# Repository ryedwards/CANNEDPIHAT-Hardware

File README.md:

# CANNEDPIHAT-Hardware

## The CannedPi Hardware
Meet the CannedPi hardware!  This simple (and not prefectly designed) Raspberry PI Hat contains an STM32G4 microcontroller which can interface with the USB port of your Pi.

Why would I create such a Rube Goldberg design??
- I wanted a HAT that would provide provide solid 5V power from a ~12V power input.  This board has a 4A SMPS that provides more than enough juice for even a power hungry Pi4.
- I wanted the option of running both scripts on the Pi (Python-CAN, C applications, etc) while also having the ability to run real-time CAN on the embedded chip as needed.
- Wanted an "all-in-one" form factor for mounting on LCD displays and other small cases
- For LIN you really need the real time microcontroller
- I wanted to prove I could do it.  Now that I feel I've achived my goal I decided to share it wth everyone

## Features
- The 26-pin header provides access to all 3 CAN channels, the LIN channel, 12V, 5V, 3.3V and a few GPIO from both the PI and the SMT32G4.  Why a 26-pin?  Other CAN tools I'm using also utilize this header and I didn't feel like making new harnesses.  Besides, it's a nice form factor for getting a lot of I/O and there are cables available on Amazon.

## Notes
This design is provided in KiCad 6.0

## Disclaimers
It has not been EMI or EMC tested.  I am not a hardware engineer so I can't ensure that there aren't some design flaws.  I've sanity tested the prototypes and they seem to be stable and perform as expected.

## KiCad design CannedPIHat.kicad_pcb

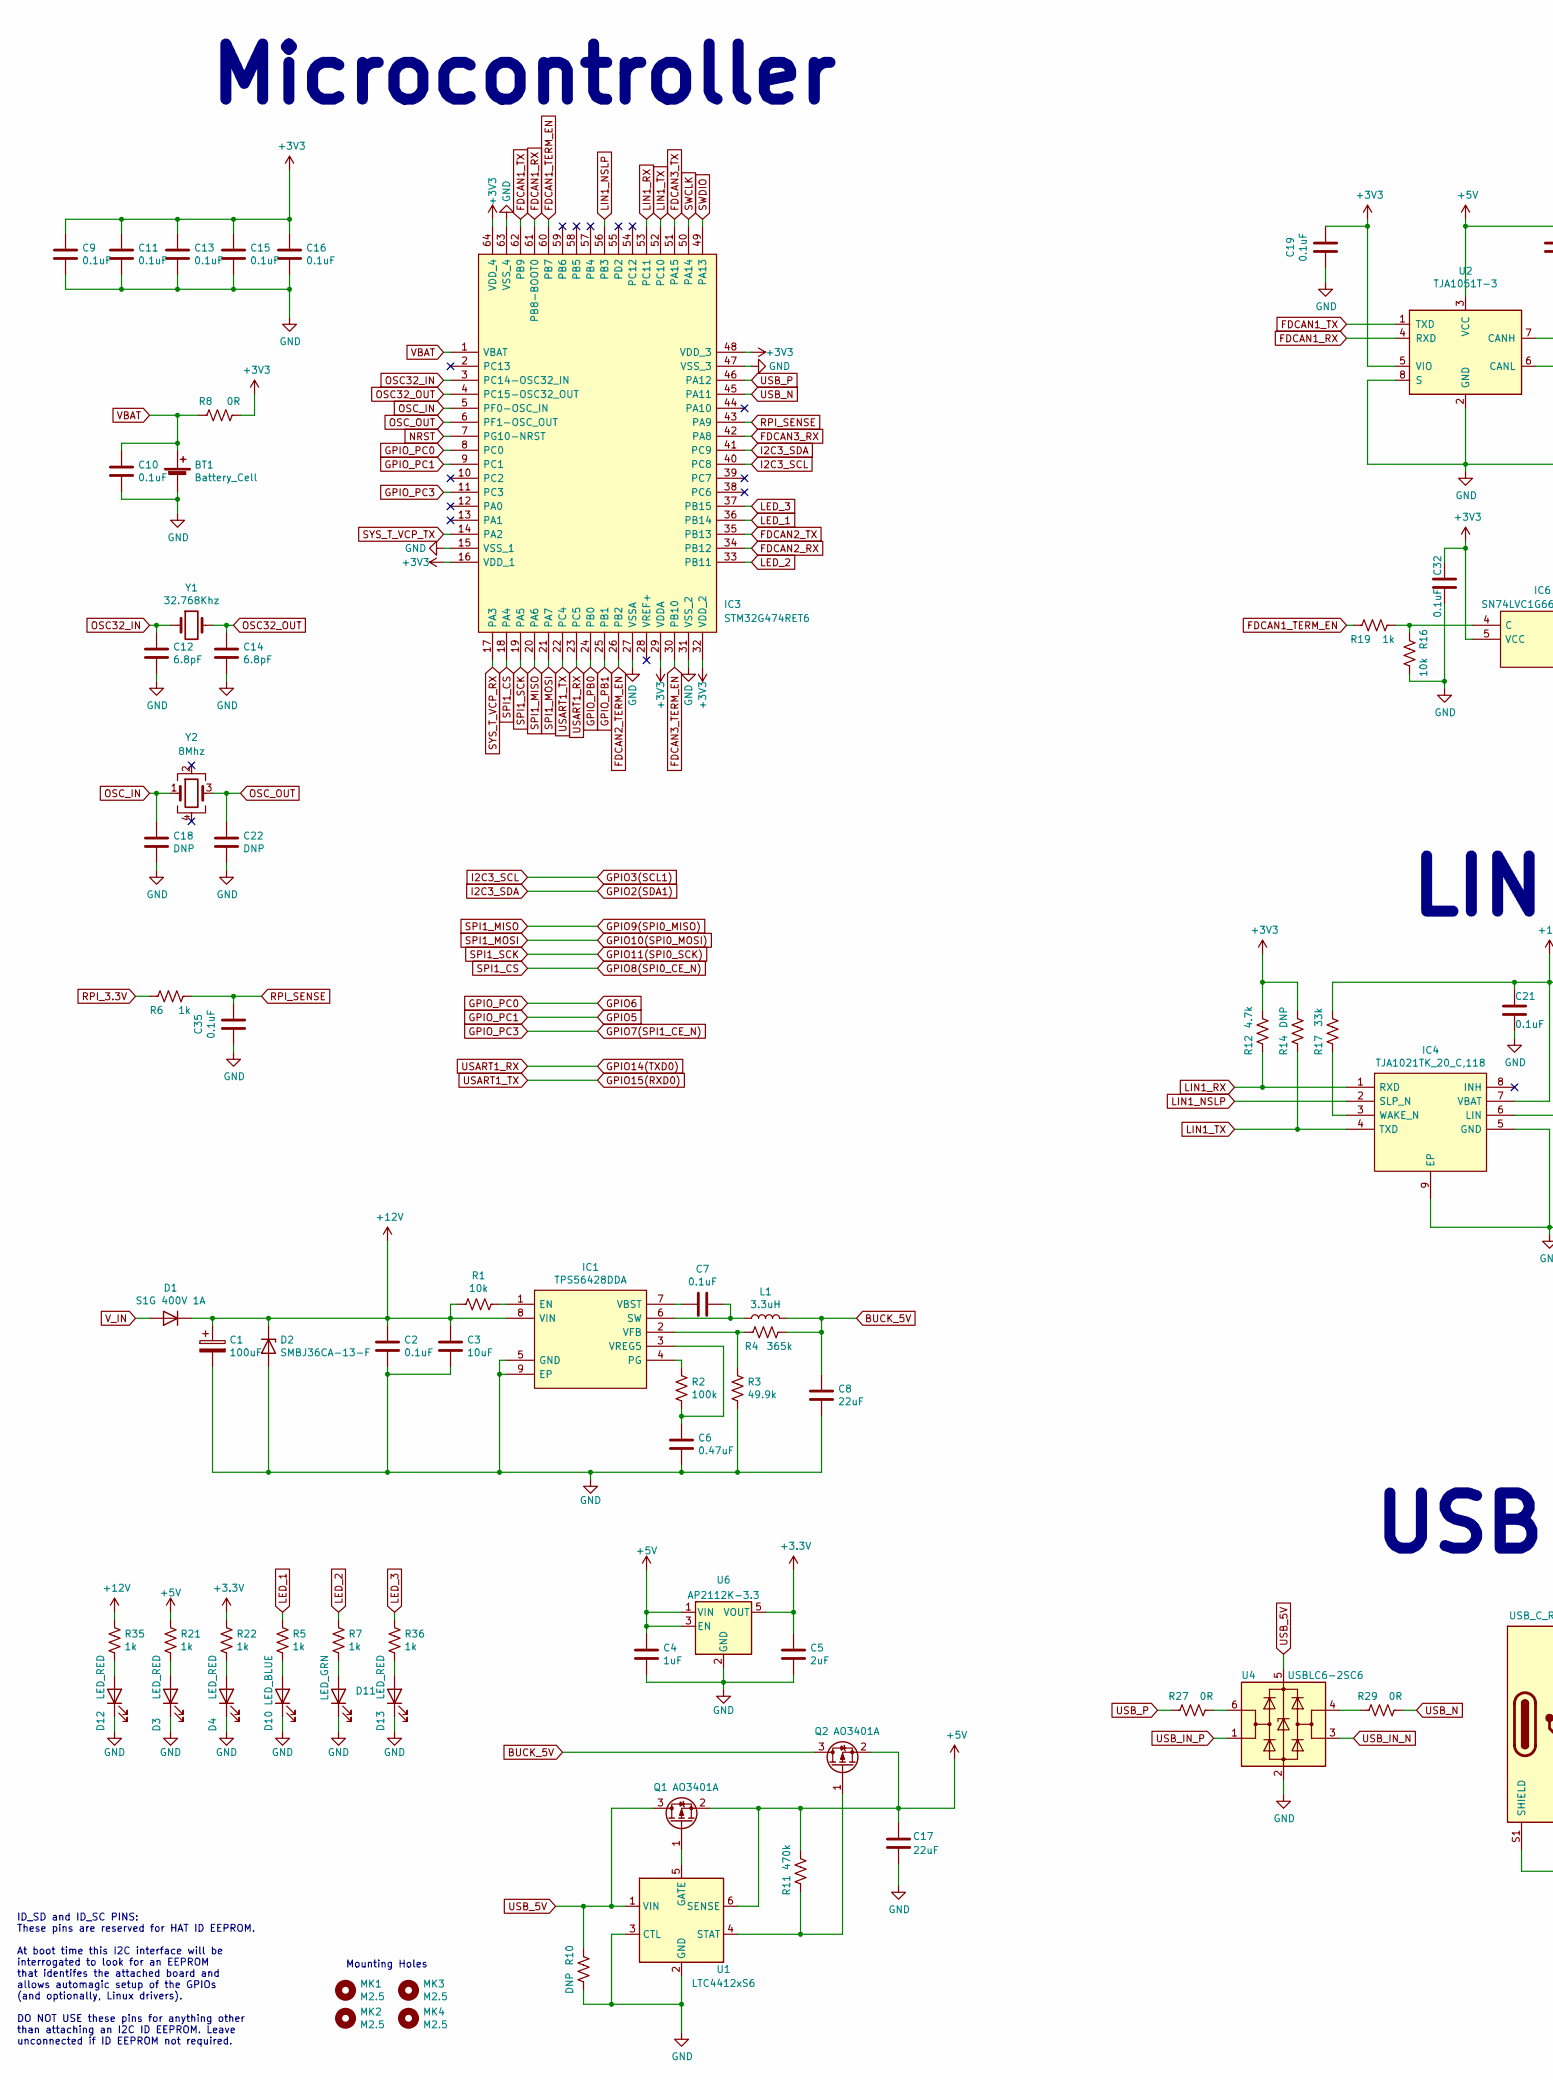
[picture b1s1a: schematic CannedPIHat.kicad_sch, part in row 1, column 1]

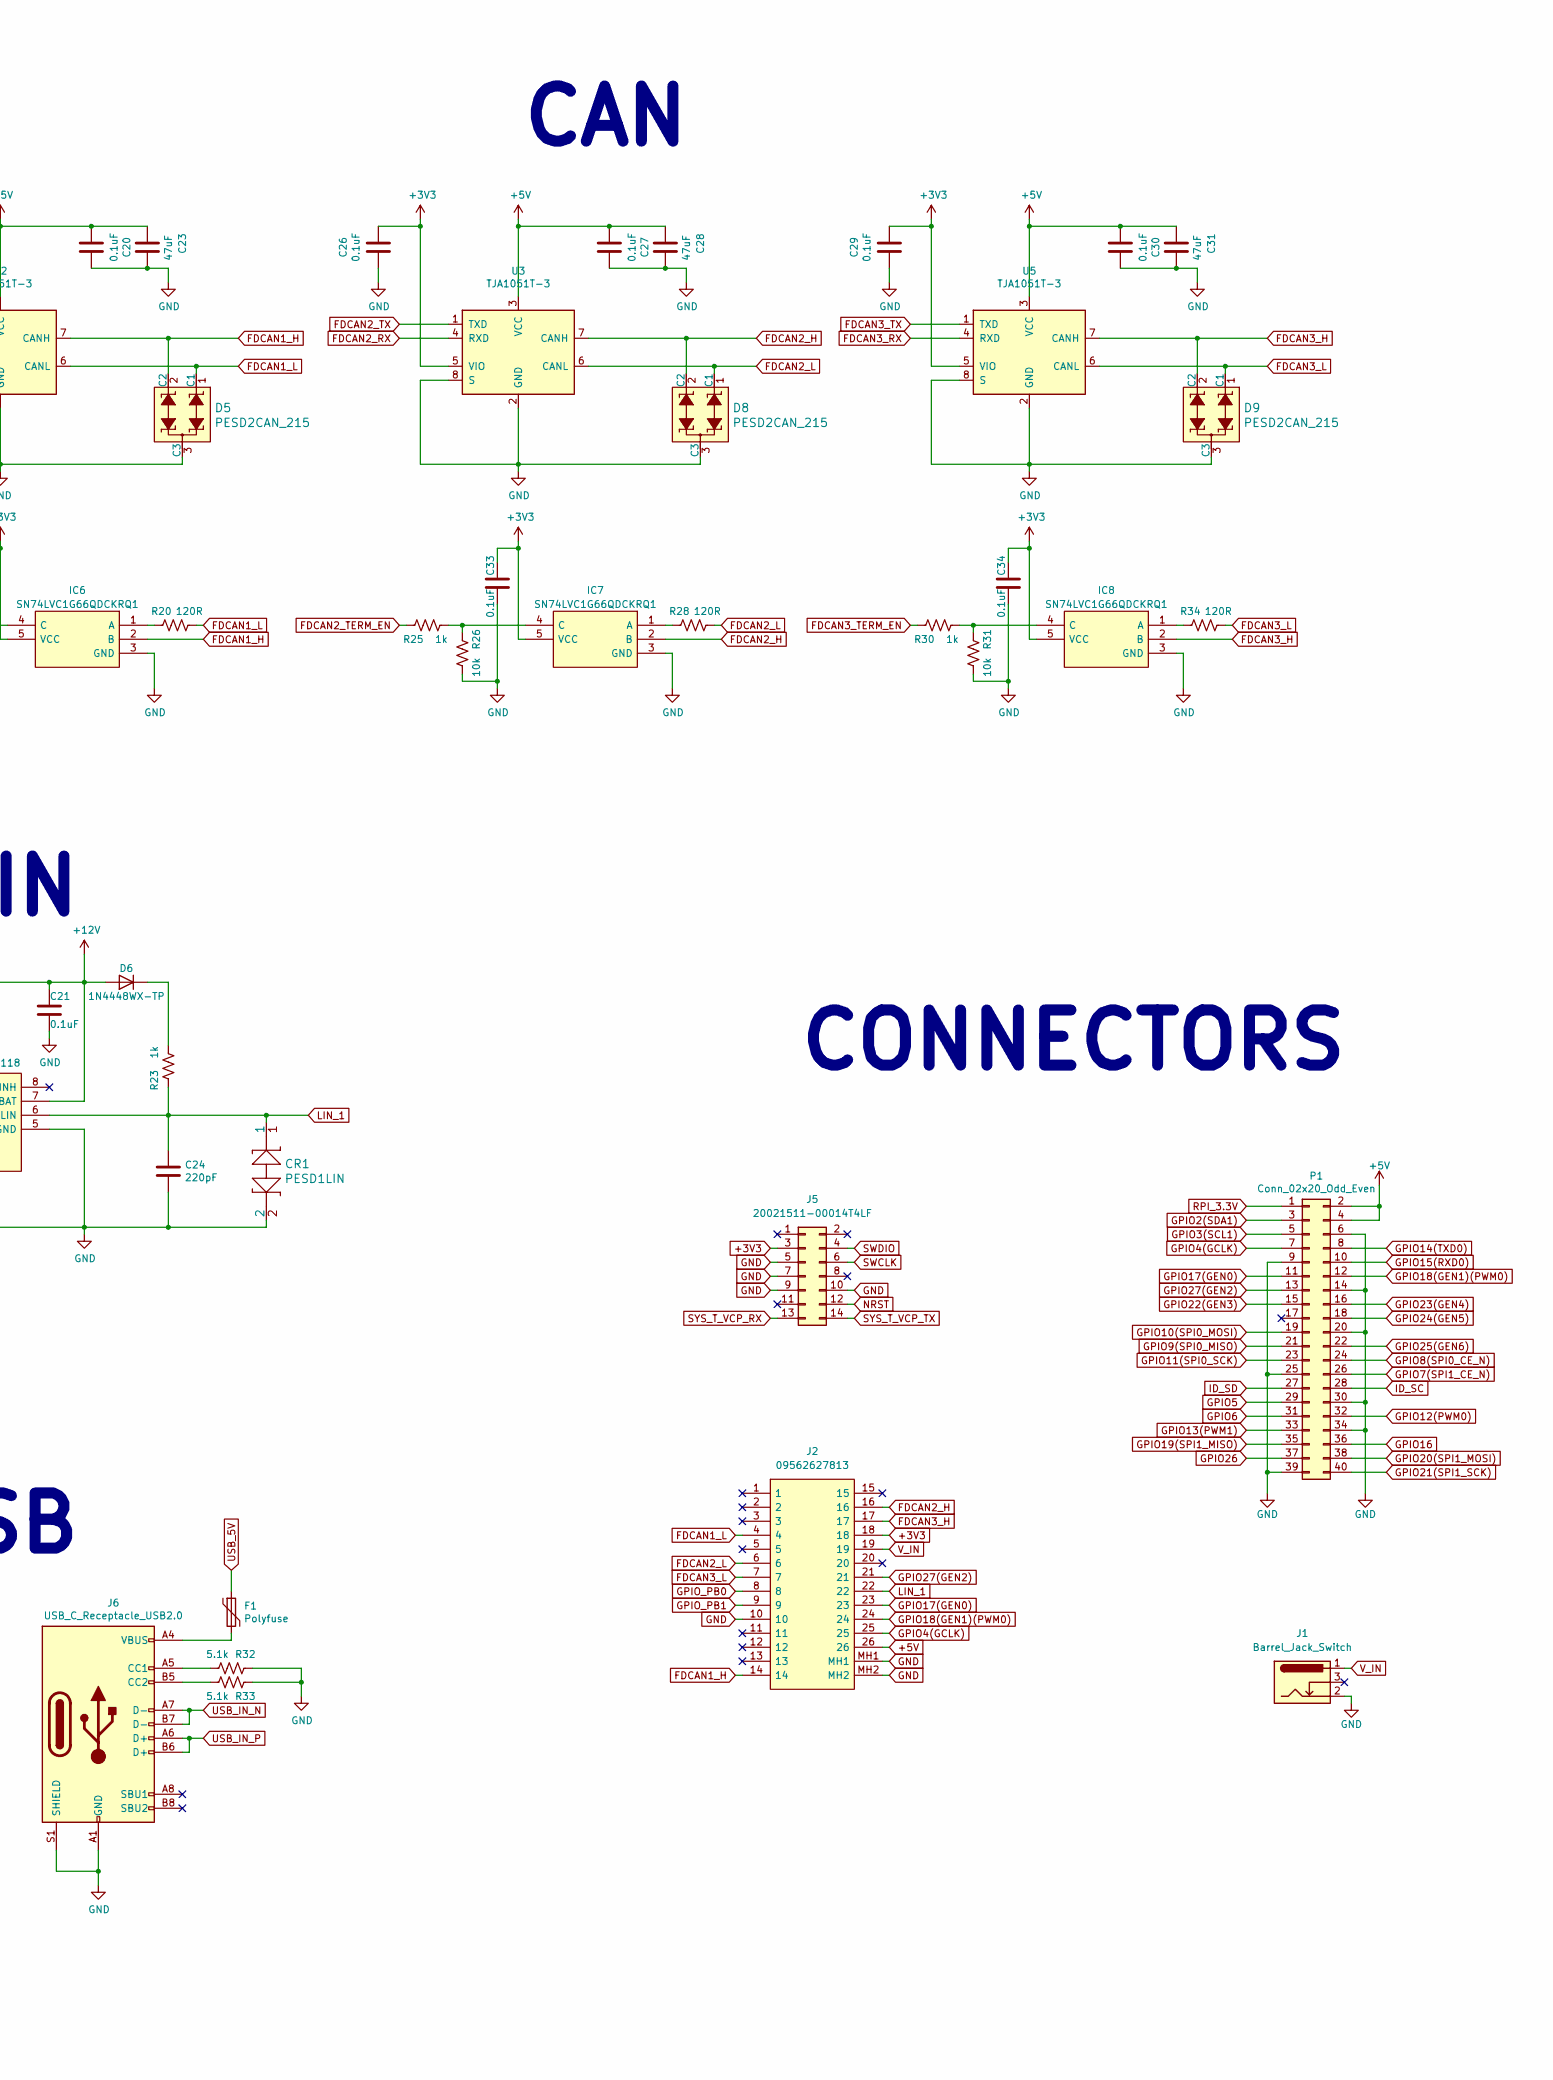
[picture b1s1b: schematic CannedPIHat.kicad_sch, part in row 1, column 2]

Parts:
BT1: Battery_Cell; S8411-45R_1; Manufacturer_Part_Number S8411-45R; Digi-Key_PN 952-1745-1-ND
C1: 100uF; CP_Elec_6.3x7.7; Manufacturer_Part_Number EMZA250ADA101MF80G; LCSC Part # C127971
C2, C7, C9, C10, C11, C13, C15, C16, C19, C20, C21, C26, C27, C29, C30, C32, C33, C34, C35: 0.1uF; C_0603_1608Metric; Manufacturer_Part_Number CC0603KRX7R8BB104; LCSC Part # C14663
C3: 10uF; C_1206_3216Metric; Manufacturer_Part_Number CL31B106KQHNFNE; LCSC Part # C13585
C4: 1uF; C_0603_1608Metric; Manufacturer_Part_Number CC0603KRX7R8BB104; LCSC Part # C14663
C5: 2uF; C_0603_1608Metric; Manufacturer_Part_Number CC0603KRX7R8BB104; LCSC Part # C14663
C6: 0.47uF; C_0603_1608Metric; Manufacturer_Part_Number CGA3E2X7R2A472K080AA; LCSC Part # C2167812
C8, C17: 22uF; C_1206_3216Metric; Manufacturer_Part_Number EMK316ABJ226ML-T; LCSC Part # C12891
C12, C14: 6.8pF; C_0402_1005Metric; Manufacturer_Part_Number GRM1555C1H6R8CA01D; LCSC Part # C1576
C18, C22: DNP; C_0402_1005Metric; LCSC Part # C1576
C23, C28, C31: 47uF; C_0805_2012Metric; Manufacturer_Part_Number JMK212BBJ476MG-T; LCSC Part # C16780
C24: 220pF; C_0603_1608Metric; Manufacturer_Part_Number CC0603JRNPO9BN221; LCSC Part # C1603
CR1: PESD1LIN; D_SOD-323_HandSoldering; Manufacturer_Part_Number PESD1LIN,135; LCSC Part # C2831530
D1: S1G 400V 1A; D_SMA; Manufacturer_Part_Number S1G; LCSC Part # C412437
D2: SMBJ36CA-13-F; D_SMB; Manufacturer_Part_Number SMBJ36CA-13-F; LCSC Part # C78421
D3, D4, D12, D13: LED_RED; LED_0603_1608Metric; Manufacturer_Part_Number LS Q976-NR-1; LCSC Part # C2286
D5, D8, D9: PESD2CAN_215; SOT-23; MPN PESD2CAN,215; Digi-Key_PN 1727-3891-1-ND
D6: ‎1N4448WX-TP‎; D_SOD-323_HandSoldering; Manufacturer_Part_Number ‎1N4448WX-TP‎; Digi-Key_PN 1N4448WXTPMSCT-ND
D10: LED_BLUE; LED_0603_1608Metric; Manufacturer_Part_Number LB Q39E-N1OO-35-1; LCSC Part # C72041
D11: LED_GRN; LED_0603_1608Metric; Manufacturer_Part_Number LG Q396-PS-35; LCSC Part # C72043
F1: Polyfuse; Fuse_0805_2012Metric; Manufacturer_Part_Number 0ZCK0035FF2G; LCSC Part # C369150
IC1: TPS56428DDA; SOIC-8-1EP_3.9x4.9mm_P1.27mm_EP2.29x3mm_ThermalVias; Mouser Part Number 595-TPS56428DDA
IC3: STM32G474RET6; LQFP-64_10x10mm_P0.5mm; Mouser Part Number 511-STM32G474RET6
IC4: TJA1021TK_20_C,118; HVSON-8-1EP_3x3mm_P0.65mm_EP1.6x2.4mm; Mouser Part Number 771-TJA1021TK20C1
IC6, IC7, IC8: SN74LVC1G66QDCKRQ1; SOT-665; Mouser Part Number 595-LVC1G66QDCKRQ1
J1: Barrel_Jack_Switch; BarrelJack_Horizontal
J2: 09562627813; Manufacturer_Part_Number 09562627813; Mouser Part Number 617-09-56-262-7813
J5: 20021511-00014T4LF; PinHeader_2x07_P1.27mm_Vertical; Mouser Part Number 200-FTSH10701LDK
J6: USB_C_Receptacle_USB2.0; USB_C_Receptacle_GCT_USB4085; Manufacturer_Part_Number USB4085-GF-A; Digi-Key_PN 2073-USB4085-GF-ACT-ND
L1: 3.3uH; L_Taiyo-Yuden_NR-50xx; LCSC Part # C167908
MK1, MK2, MK3, MK4: M2.5; MountingHole_2.7mm_M2.5
P1: Conn_02x20_Odd_Even; M207812045_MIRROR; Manufacturer_Part_Number M20-7812045R; Digi-Key_PN 952-3230-2-ND
Q1, Q2: AO3401A; SOT-23; LCSC Part # C15127
R1, R16, R26, R31: 10k; R_0603_1608Metric; Manufacturer_Part_Number RC0603FR-0710KL; LCSC Part # C25804
R2: 100k; R_0603_1608Metric; Manufacturer_Part_Number RC0603FR-07100KL; LCSC Part # C25803
R3: 49.9k; R_0603_1608Metric; Manufacturer_Part_Number AF0603FR-0749K9L; LCSC Part # C23184
R4: 365k; R_0603_1608Metric; Manufacturer_Part_Number 13-AC0603FR-07365KLCT-ND; LCSC Part # C23031
R5, R6, R7, R19, R21, R22, R23, R25, R30, R35, R36: 1k; R_0603_1608Metric; Manufacturer_Part_Number RC0603FR-071KL; LCSC Part # C21190
R8, R27, R29: 0R; R_0603_1608Metric; Manufacturer_Part_Number RC0603JR-070RL; LCSC Part # C21189
R10: DNP; R_0402_1005Metric
R11: 470k; R_0603_1608Metric; LCSC Part # C23178
R12: 4.7k; R_0603_1608Metric; Manufacturer_Part_Number RC0603JR-074K7L; LCSC Part # C23162
R14: DNP; R_0603_1608Metric
R17: 33k; R_0603_1608Metric; Manufacturer_Part_Number RC0603FR-0733K2L; LCSC Part # C4216
R20, R28, R34: 120R; R_0603_1608Metric; Manufacturer_Part_Number RC0603FR-07120RL; LCSC Part # C22787
R32, R33: 5.1k; R_0603_1608Metric; Manufacturer_Part_Number RC0603JR-075K1L; LCSC Part # C23186
U1: LTC4412xS6; TSOT-23-6; LCSC Part # C514442
U2, U3, U5: TJA1051T-3; SOIC-8_3.9x4.9mm_P1.27mm; LCSC Part # C38695
U4: USBLC6-2SC6; SOT-23-6; Manufacturer_Part_Number USBLC6-2SC6; LCSC Part # C2687116
U6: AP2112K-3.3; SOT-23-5
Y1: 32.768Khz; Crystal_SMD_2012-2Pin_2.0x1.2mm; Manufacturer_Part_Number ECS-.327-6-12-C-TR; LCSC Part # C276423
Y2: 8Mhz; Crystal_SMD_3225-4Pin_3.2x2.5mm

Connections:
+5V: C4.1, C17.1, C20.2, C23.1, C27.2, C28.1, C30.2, C31.1, J2.26, P1.2, P1.4, Q1.2 (S), Q2.2 (S), R11.2, R21.2, U1.6 (SENSE), U2.3 (VCC), U3.3 (VCC), U5.3 (VCC), U6.1 (VIN), U6.3 (EN)
+12V: C1.1, C2.1, C3.1, C21.1, D1.1 (K), D2.1 (K), D6.2 (A), IC1.8 (VIN), IC4.7 (VBAT), R1.2, R17.2, R35.2
BUCK_5V: C8.1, L1.2, Q2.3 (D), R4.1
FDCAN1_H: D5.2 (C2), IC6.2 (B), J2.14, U2.7 (CANH)
FDCAN1_L: D5.1 (C1), J2.4, R20.2, U2.6 (CANL)
FDCAN1_RX: IC3.61 (PB8-BOOT0), U2.4 (RXD)
FDCAN1_TERM_EN: IC3.60 (PB7), R19.1
FDCAN1_TX: IC3.62 (PB9), U2.1 (TXD)
FDCAN2_H: D8.2 (C2), IC7.2 (B), J2.16, U3.7 (CANH)
FDCAN2_L: D8.1 (C1), J2.6, R28.2, U3.6 (CANL)
FDCAN2_RX: IC3.34 (PB12), U3.4 (RXD)
FDCAN2_TERM_EN: IC3.26 (PB2), R25.1
FDCAN2_TX: IC3.35 (PB13), U3.1 (TXD)
FDCAN3_H: D9.2 (C2), IC8.2 (B), J2.17, U5.7 (CANH)
FDCAN3_L: D9.1 (C1), J2.7, R34.2, U5.6 (CANL)
FDCAN3_RX: IC3.42 (PA8), U5.4 (RXD)
FDCAN3_TERM_EN: IC3.30 (PB10), R30.1
FDCAN3_TX: IC3.51 (PA15), U5.1 (TXD)
GND: BT1.2 (-), C1.2, C2.2, C3.2, C4.2, C5.2, C6.2, C8.2, C9.2, C10.2, C11.2, C12.2, C13.2, C14.2, C15.2, C16.2, C17.2, C18.2, C19.2, C20.1, C21.2, C22.2, C23.2, C24.2, C26.2, C27.1, C28.2, C29.2, C30.1, C31.2, C32.2, C33.2, C34.2, C35.2, CR1.2, D2.2 (A), D3.1 (K), D4.1 (K), D5.3 (C3), D8.3 (C3), D9.3 (C3), D10.1 (K), D11.1 (K), D12.1 (K), D13.1 (K), IC1.5 (GND), IC1.9 (EP), IC3.15 (VSS_1), IC3.27 (VSSA), IC3.31 (VSS_2), IC3.47 (VSS_3), IC3.63 (VSS_4), IC4.5 (GND), IC4.9 (EP), IC6.3 (GND), IC7.3 (GND), IC8.3 (GND), J1.2, J2.10, J2.MH1, J2.MH2, J5.5, J5.7, J5.9, J5.10, J6.A1 (GND), J6.A12 (GND), J6.B1 (GND), J6.B12 (GND), J6.S1 (SHIELD), P1.6, P1.9, P1.14, P1.20, P1.25, P1.30, P1.34, P1.39, R3.2, R10.2, R16.2, R26.2, R31.2, R32.1, R33.1, U1.2 (GND), U1.3 (CTL), U2.2 (GND), U2.8 (S), U3.2 (GND), U3.8 (S), U4.2 (GND), U5.2 (GND), U5.8 (S), U6.2 (GND)
GPIO2(SDA1): IC3.41 (PC9), P1.3
GPIO3(SCL1): IC3.40 (PC8), P1.5
GPIO4(GCLK): J2.25, P1.7
GPIO5: IC3.9 (PC1), P1.29
GPIO6: IC3.8 (PC0), P1.31
GPIO7(SPI1_CE_N): IC3.11 (PC3), P1.26
GPIO8(SPI0_CE_N): IC3.18 (PA4), P1.24
GPIO9(SPI0_MISO): IC3.20 (PA6), P1.21
GPIO10(SPI0_MOSI): IC3.21 (PA7), P1.19
GPIO11(SPI0_SCK): IC3.19 (PA5), P1.23
GPIO12(PWM0): P1.32
GPIO13(PWM1): P1.33
GPIO14(TXD0): IC3.23 (PC5), P1.8
GPIO15(RXD0): IC3.22 (PC4), P1.10
GPIO16: P1.36
GPIO17(GEN0): J2.23, P1.11
GPIO18(GEN1)(PWM0): J2.24, P1.12
GPIO19(SPI1_MISO): P1.35
GPIO20(SPI1_MOSI): P1.38
GPIO21(SPI1_SCK): P1.40
GPIO22(GEN3): P1.15
GPIO23(GEN4): P1.16
GPIO24(GEN5): P1.18
GPIO25(GEN6): P1.22
GPIO26: P1.37
GPIO27(GEN2): J2.21, P1.13
GPIO_PB0: IC3.24 (PB0), J2.8
GPIO_PB1: IC3.25 (PB1), J2.9
ID_SC: P1.28
ID_SD: P1.27
LED_1: IC3.36 (PB14), R5.2
LED_2: IC3.33 (PB11), R7.2
LED_3: IC3.37 (PB15), R36.2
LIN1_NSLP: IC3.56 (PB3), IC4.2 (SLP_N)
LIN1_RX: IC3.53 (PC11), IC4.1 (RXD), R12.1
LIN1_TX: IC3.52 (PC10), IC4.4 (TXD), R14.1
LIN_1: C24.1, CR1.1, IC4.6 (LIN), J2.22, R23.1
NRST: IC3.7 (PG10-NRST), J5.12
unnamed: C6.1, IC1.3 (VREG5), R2.2
unnamed: C7.1, IC1.6 (SW), L1.1
unnamed: C7.2, IC1.7 (VBST)
unnamed: D3.2 (A), R21.1
unnamed: D4.2 (A), R22.1
unnamed: D6.1 (K), R23.2
unnamed: D10.2 (A), R5.1
unnamed: D11.2 (A), R7.1
unnamed: D12.2 (A), R35.1
unnamed: D13.2 (A), R36.1
unnamed: F1.2, J6.A4 (VBUS), J6.A9 (VBUS), J6.B4 (VBUS), J6.B9 (VBUS)
unnamed: IC1.1 (EN), R1.1
unnamed: IC1.2 (VFB), R3.1, R4.2
unnamed: IC1.4 (PG), R2.1
unnamed: IC4.3 (WAKE_N), R17.1
unnamed: IC6.1 (A), R20.1
unnamed: IC6.4 (C), R16.1, R19.2
unnamed: IC7.1 (A), R28.1
unnamed: IC7.4 (C), R25.2, R26.1
unnamed: IC8.1 (A), R34.1
unnamed: IC8.4 (C), R30.2, R31.1
unnamed: J6.A5 (CC1), R32.2
unnamed: J6.B5 (CC2), R33.2
unnamed: Q1.1 (G), U1.5 (GATE)
unnamed: Q2.1 (G), R11.1, U1.4 (STAT)
unnamed: R27.2, U4.6 (I/O1)
unnamed: R29.1, U4.4 (I/O2)
OSC32_IN: C12.1, IC3.3 (PC14-OSC32_IN), Y1.1
OSC32_OUT: C14.1, IC3.4 (PC15-OSC32_OUT), Y1.2
OSC_IN: C18.1, IC3.5 (PF0-OSC_IN), Y2.1
OSC_OUT: C22.1, IC3.6 (PF1-OSC_OUT), Y2.3
RPI_3.3V: P1.1, R6.1
RPI_SENSE: C35.1, IC3.43 (PA9), R6.2
SWCLK: IC3.50 (PA14), J5.6
SWDIO: IC3.49 (PA13), J5.4
SYS_T_VCP_RX: IC3.17 (PA3), J5.13
SYS_T_VCP_TX: IC3.14 (PA2), J5.14
USB_5V: F1.1, Q1.3 (D), R10.1, U1.1 (VIN), U4.5 (VBUS)
USB_IN_N: J6.A7 (D-), J6.B7 (D-), U4.3 (I/O2)
USB_IN_P: J6.A6 (D+), J6.B6 (D+), U4.1 (I/O1)
USB_N: IC3.45 (PA11), R29.2
USB_P: IC3.46 (PA12), R27.1
VBAT: BT1.1 (+), C10.1, IC3.1 (VBAT), R8.1
V_IN: D1.2 (A), J1.1, J2.19

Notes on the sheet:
Mounting Holes
CAN
LIN
Microcontroller
USB
CONNECTORS
ID_SD and ID_SC PINS: These pins are reserved for HAT ID EEPROM. At boot time this I2C interface will be interrogated to look for an EEPROM that identifes the attached board and allows automagic setup of the GPIOs (and optionally, Linux drivers). DO NOT USE these pins for anything other than attach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

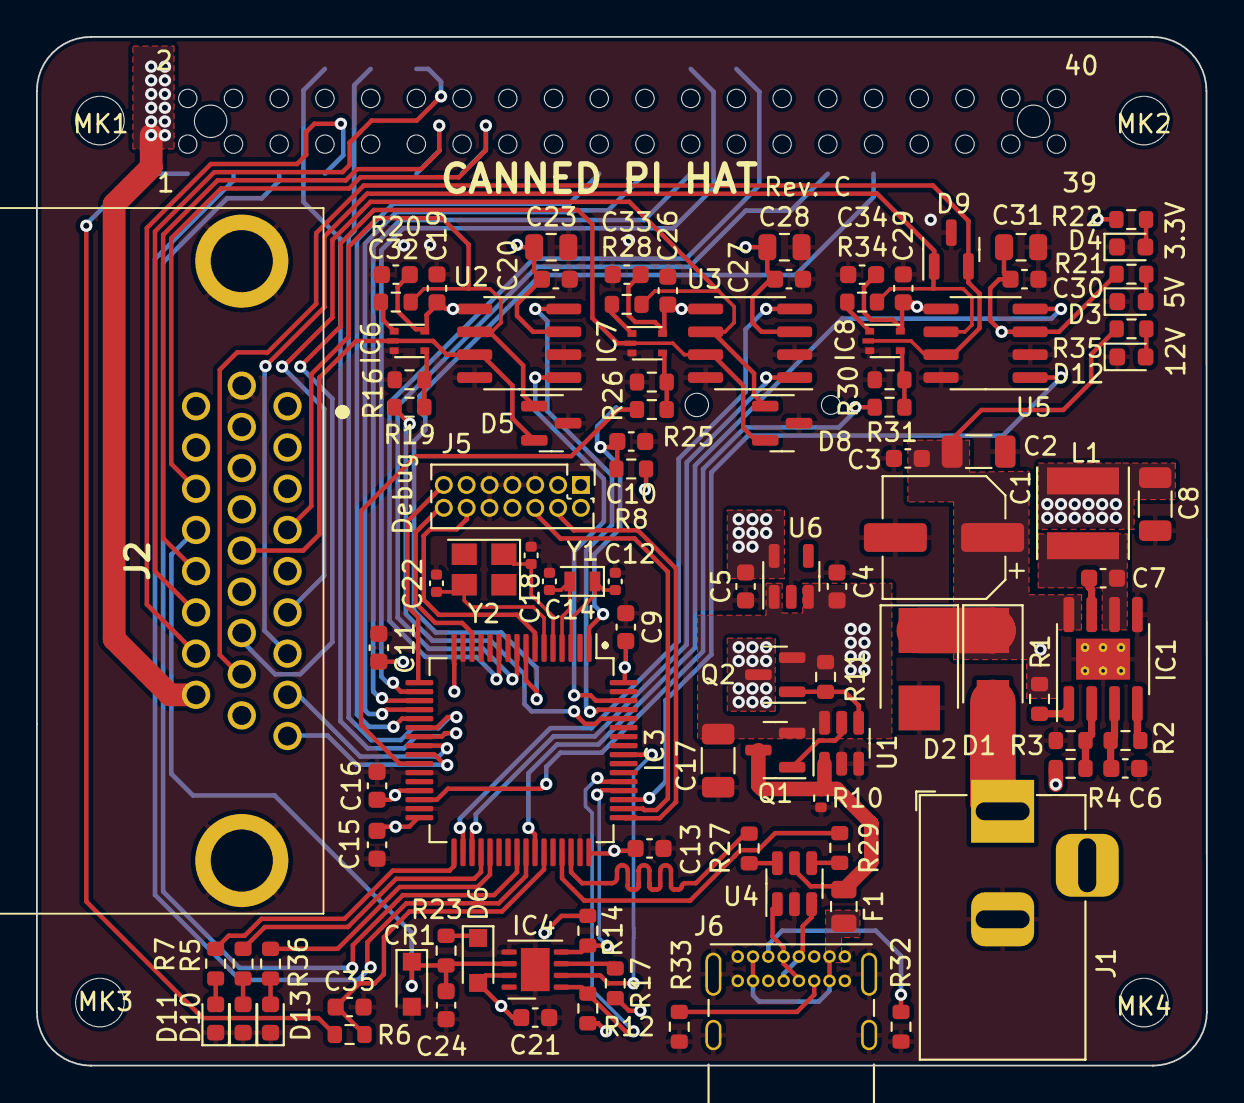
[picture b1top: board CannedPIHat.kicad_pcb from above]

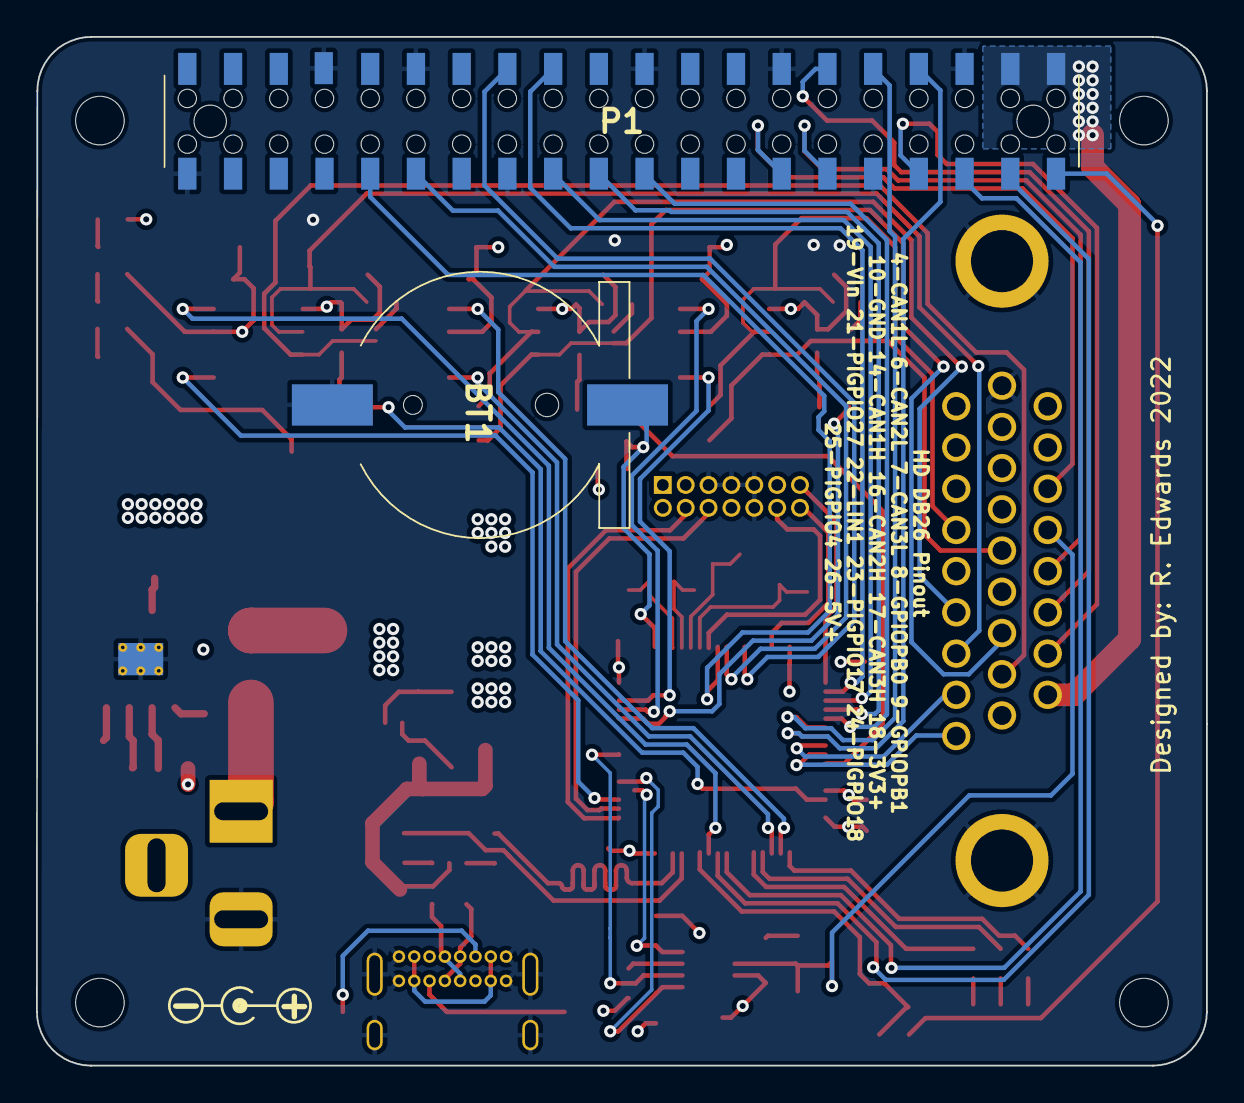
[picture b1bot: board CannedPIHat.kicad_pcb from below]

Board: 4 copper layers, 65.0 x 57.2 mm, 106 parts (2 on the bottom side), 89 nets.

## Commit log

2022-01-23 Add an image of the board
2022-01-29 Update to Rev C.
2022-01-29 Fix silkscreen
